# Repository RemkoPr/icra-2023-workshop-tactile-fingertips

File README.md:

# ICRA2023 Transferability in Robotics Workshop 
## Augmenting Off-the-Shelf Grippers with Tactile Sensing
[Paper](https://doi.org/10.48550/arXiv.2306.05902) -- [Related work](https://doi.org/10.1109/LRA.2023.3284382)

The development of tactile sensing ad its fusion with computer vision is expected to enhance robotic systems in handling complex tasks like deformable object manipulation. However, readily available industrial grippers typically lack tactile feedback, which has led researchers to integrate and develop their own tactile sensors. This has resulted in a wide range of sensor hardware and difficulty in comparing tasksolving performance. We propose moving towards accessible open-source sensors and present a set of fingertips specifically designed for fine object manipulation, with readily interpretable data output. The fingertips are validated through two difficult tasks: cloth edge tracing and cable tracing. 

## Video material
Video material of the proof-of-concept experiments is provided in the videos folder.

## Hardware integration

Currently the fingertips are designed for the Robotiq-2F85 gripper. This gripper can be mounted to various different collaborative robot arms by means of a tool flange. We provide a design for an intermediate flange, nestled between the Robotiq tool flange and the gripper itself, that provides external interfaces for the supply and ground pins otherwise reserved for the gripper. This way, the sensorised fingertips can draw their power straight from the robot arm. The intermediate flange consists of a pcb in the cad/pcb folder and two 3D printed parts in the cad/3d folder. Sensor readout is currently performed by an Arduino Nano 33 BLE externally mounted to the gripper via a 3D printed holder (see cad/3d), but we are in the process of integrating a microcontroller on our custom intermediate flange such that sensor readout and data transmission can also be done internally.  

<BR CLEAR="all">

## Software integration
Both Arduino firmware and python readout software is provided. Data is communicated between the arduino and a remote workstation via Bluetooth Low Energy. Further documentation on the software is provided in the code/python folder.

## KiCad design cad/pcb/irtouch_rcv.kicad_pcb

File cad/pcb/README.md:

This folder contains PCB design files for both the receiver (irtouch_led) as well as the tranmitter (irtouch_rcv) tactile finger. Additionally, the design for the custom breakout flange (robotiq_wrist_coupling) PCB is provided. This PCB is set between the Robotiq I/O Coupling and the 2F-85 gripper itself. The arduino_breakout is a simple PCB to which female 0.1" pin headers are soldered. This PCB fits in the Arduino_holder found in cad/3d.

Refer to the cad/3d folder for an exploded view of the structural integration.

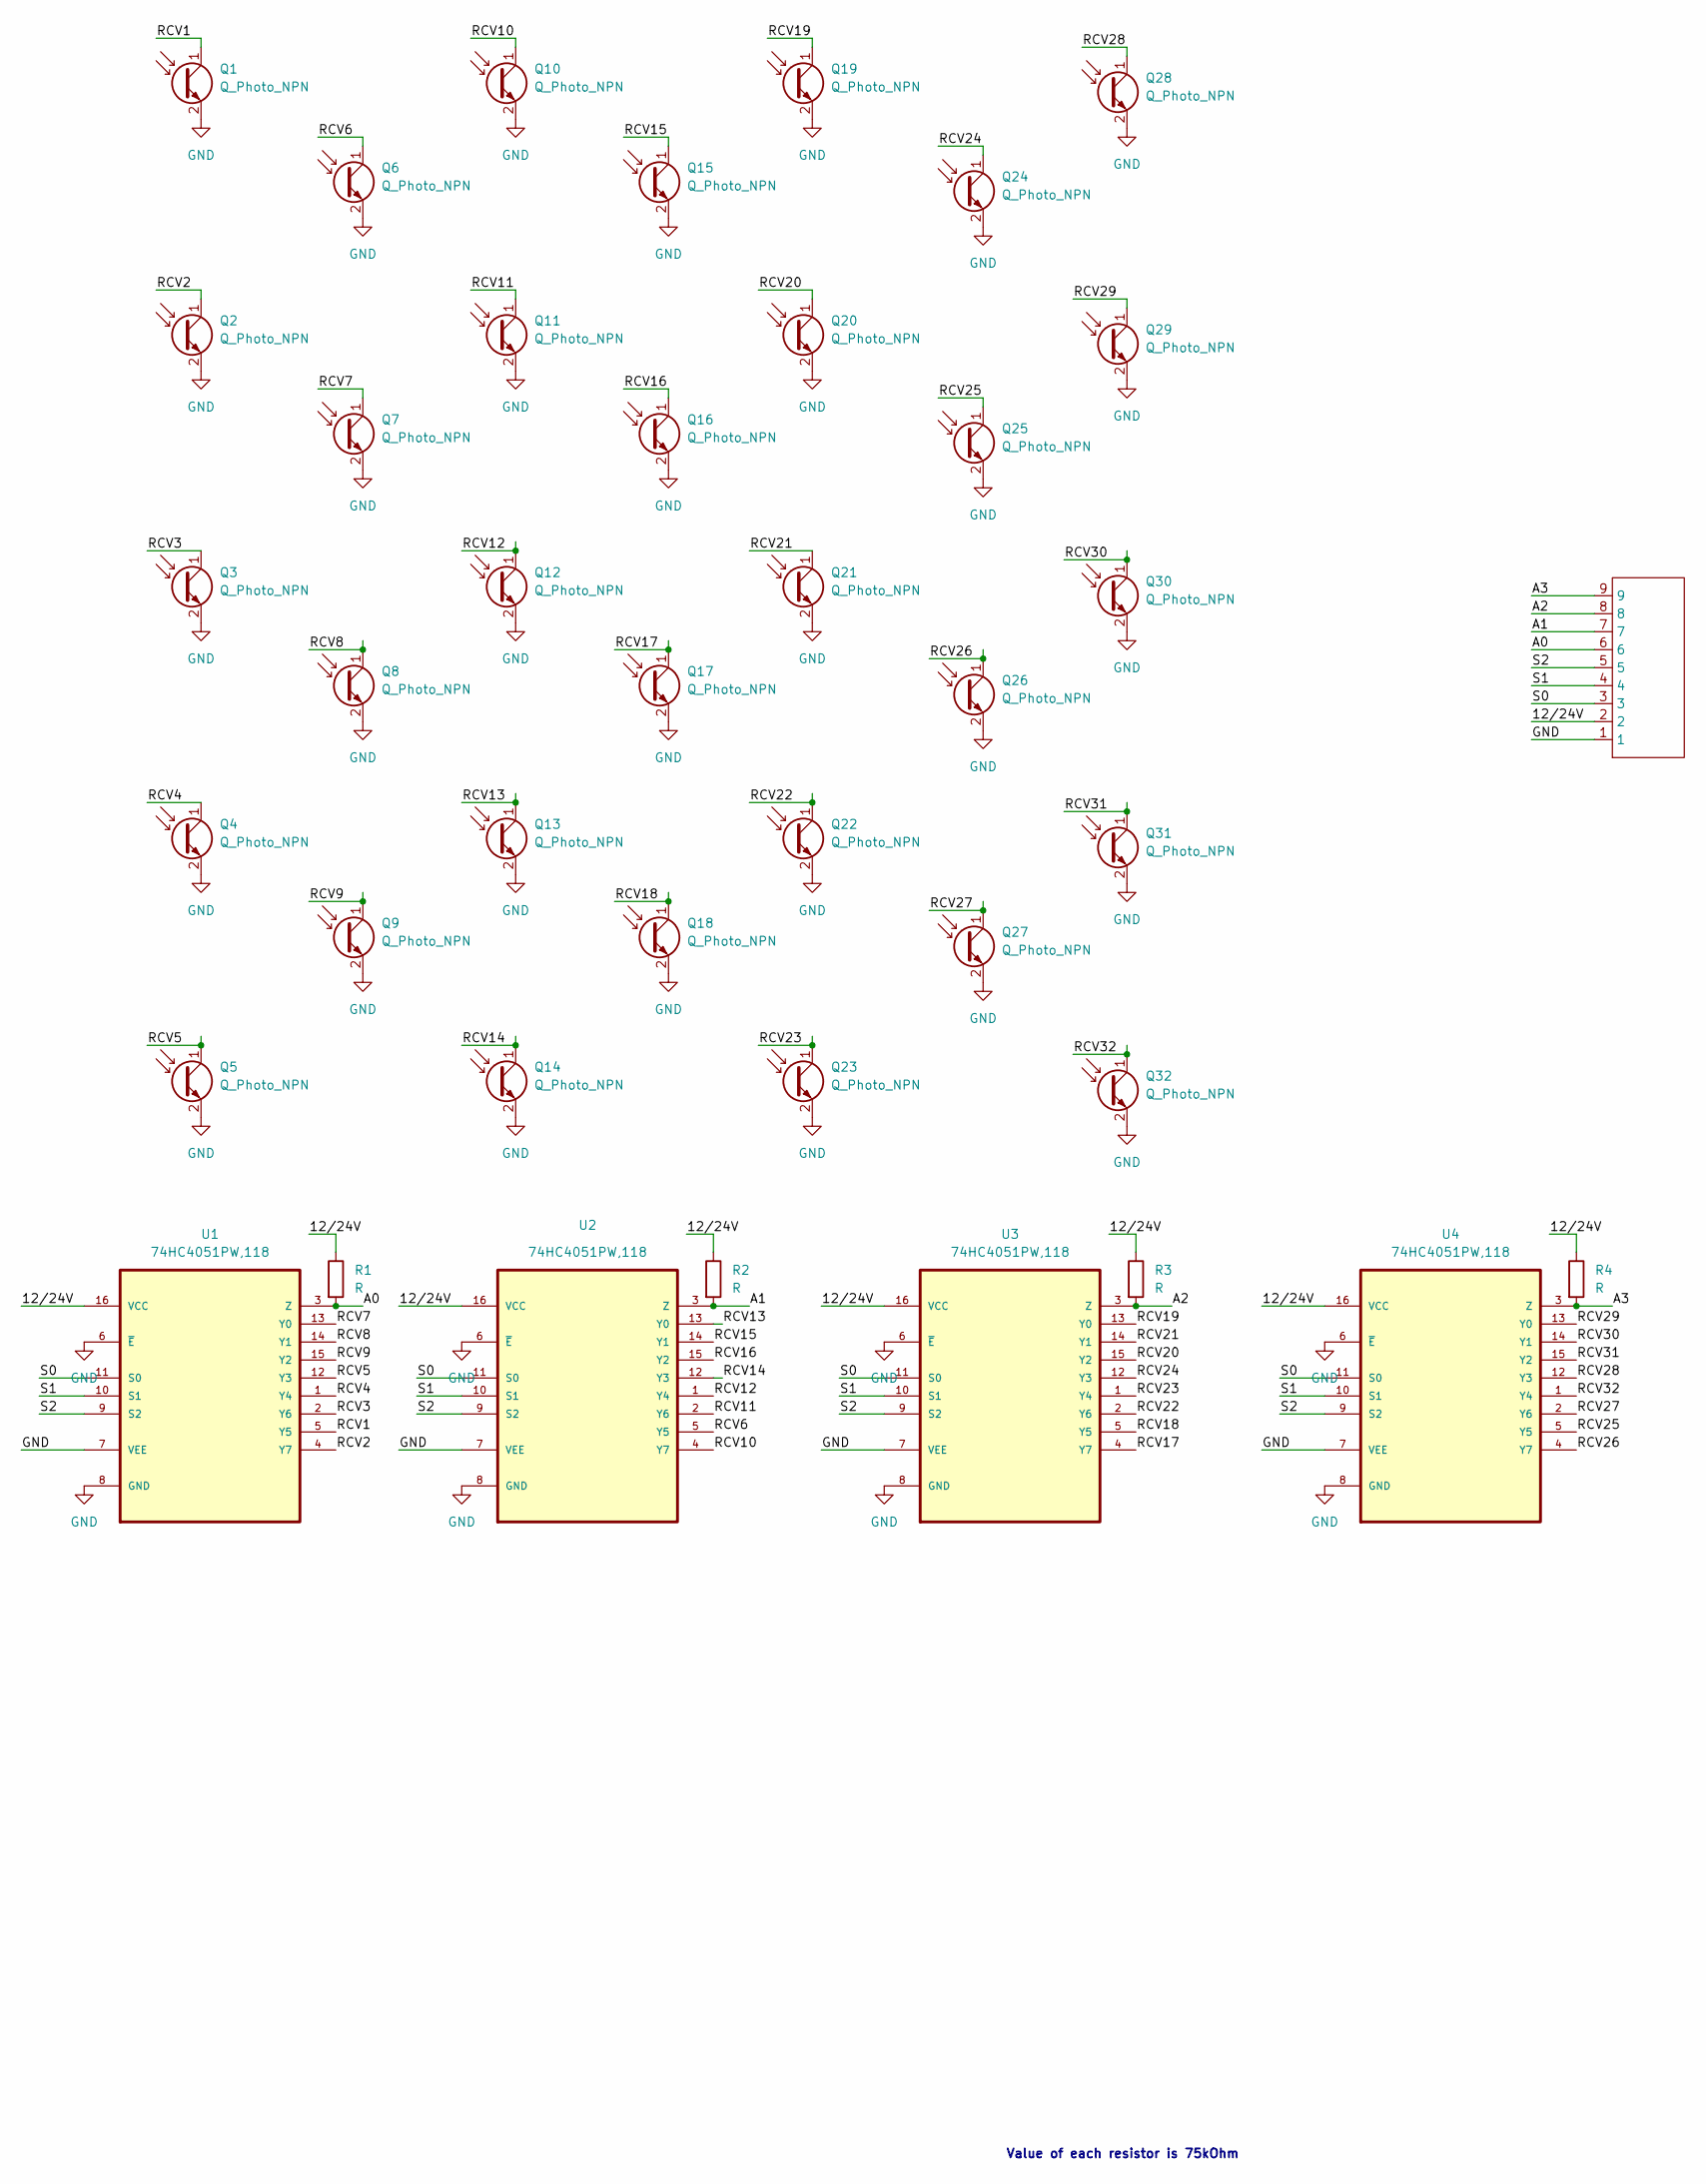
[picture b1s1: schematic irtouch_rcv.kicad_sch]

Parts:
I1: 9POS_INTERFACE
Q1, Q2, Q3, Q4, Q5, Q6, Q7, Q8, Q9, Q10, Q11, Q12, Q13, Q14, Q15, Q16, Q17, Q18, Q19, Q20, Q21, Q22, Q23, Q24, Q25, Q26, Q27, Q28, Q29, Q30, Q31, Q32: Q_Photo_NPN; RCVR
R1, R2, R3, R4: R; R0603
U1, U2, U3, U4: 74HC4051PW,118; SOP65P640X110-16N; MPN 74HC4051PW,118

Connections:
/12/24V: I1.2, R1.1, R2.1, R3.1, R4.1, U1.16 (VCC), U2.16 (VCC), U3.16 (VCC), U4.16 (VCC)
/A0: I1.6, R1.2, U1.3 (Z)
/A1: I1.7, R2.2, U2.3 (Z)
/A2: I1.8, R3.2, U3.3 (Z)
/A3: I1.9, R4.2, U4.3 (Z)
/RCV1: Q1.1 (C), U1.5 (Y5)
/RCV2: Q2.1 (C), U1.4 (Y7)
/RCV3: Q3.1 (C), U1.2 (Y6)
/RCV4: Q4.1 (C), U1.1 (Y4)
/RCV5: Q5.1 (C), U1.12 (Y3)
/RCV6: Q6.1 (C), U2.5 (Y5)
/RCV7: Q7.1 (C), U1.13 (Y0)
/RCV8: Q8.1 (C), U1.14 (Y1)
/RCV9: Q9.1 (C), U1.15 (Y2)
/RCV10: Q10.1 (C), U2.4 (Y7)
/RCV11: Q11.1 (C), U2.2 (Y6)
/RCV12: Q12.1 (C), U2.1 (Y4)
/RCV13: Q13.1 (C), U2.13 (Y0)
/RCV14: Q14.1 (C), U2.12 (Y3)
/RCV15: Q15.1 (C), U2.14 (Y1)
/RCV16: Q16.1 (C), U2.15 (Y2)
/RCV17: Q17.1 (C), U3.4 (Y7)
/RCV18: Q18.1 (C), U3.5 (Y5)
/RCV19: Q19.1 (C), U3.13 (Y0)
/RCV20: Q20.1 (C), U3.15 (Y2)
/RCV21: Q21.1 (C), U3.14 (Y1)
/RCV22: Q22.1 (C), U3.2 (Y6)
/RCV23: Q23.1 (C), U3.1 (Y4)
/RCV24: Q24.1 (C), U3.12 (Y3)
/RCV25: Q25.1 (C), U4.5 (Y5)
/RCV26: Q26.1 (C), U4.4 (Y7)
/RCV27: Q27.1 (C), U4.2 (Y6)
/RCV28: Q28.1 (C), U4.12 (Y3)
/RCV29: Q29.1 (C), U4.13 (Y0)
/RCV30: Q30.1 (C), U4.14 (Y1)
/RCV31: Q31.1 (C), U4.15 (Y2)
/RCV32: Q32.1 (C), U4.1 (Y4)
/S0: I1.3, U1.11 (S0), U2.11 (S0), U3.11 (S0), U4.11 (S0)
/S1: I1.4, U1.10 (S1), U2.10 (S1), U3.10 (S1), U4.10 (S1)
/S2: I1.5, U1.9 (S2), U2.9 (S2), U3.9 (S2), U4.9 (S2)
GND: I1.1, Q1.2 (E), Q2.2 (E), Q3.2 (E), Q4.2 (E), Q5.2 (E), Q6.2 (E), Q7.2 (E), Q8.2 (E), Q9.2 (E), Q10.2 (E), Q11.2 (E), Q12.2 (E), Q13.2 (E), Q14.2 (E), Q15.2 (E), Q16.2 (E), Q17.2 (E), Q18.2 (E), Q19.2 (E), Q20.2 (E), Q21.2 (E), Q22.2 (E), Q23.2 (E), Q24.2 (E), Q25.2 (E), Q26.2 (E), Q27.2 (E), Q28.2 (E), Q29.2 (E), Q30.2 (E), Q31.2 (E), Q32.2 (E), U1.6 (~E), U1.7 (VEE), U1.8 (GND), U2.6 (~E), U2.7 (VEE), U2.8 (GND), U3.6 (~E), U3.7 (VEE), U3.8 (GND), U4.6 (~E), U4.7 (VEE), U4.8 (GND)

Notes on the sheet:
Value of each resistor is 75kOhm

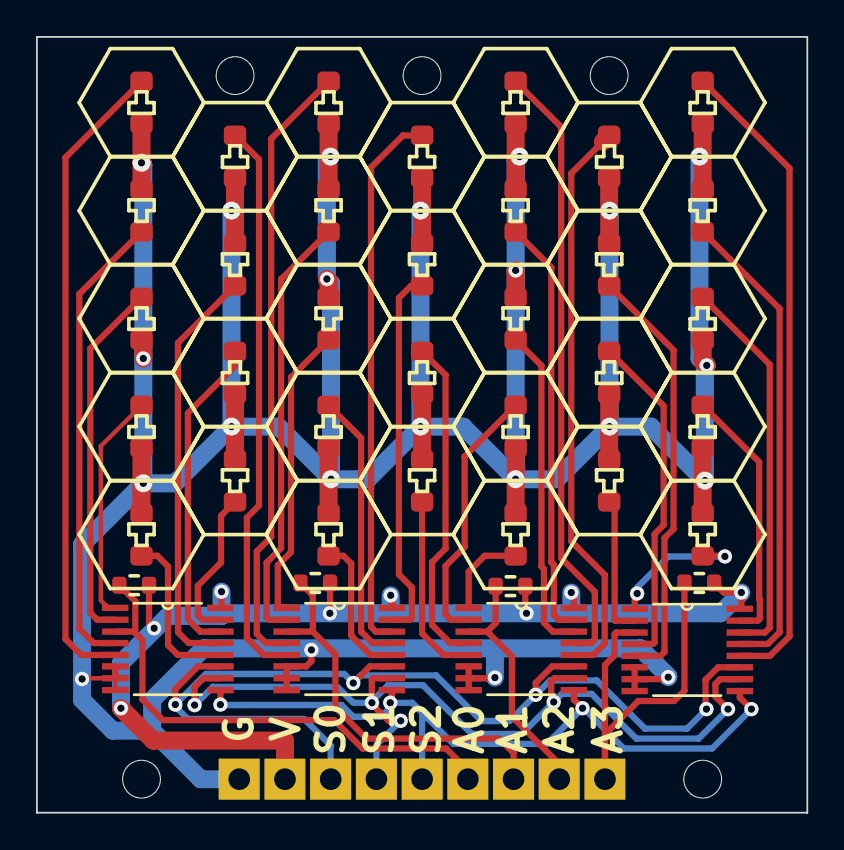
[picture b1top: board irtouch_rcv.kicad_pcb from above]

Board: 4 copper layers, 42.8 x 43.1 mm, 41 parts (0 on the bottom side), 41 nets.

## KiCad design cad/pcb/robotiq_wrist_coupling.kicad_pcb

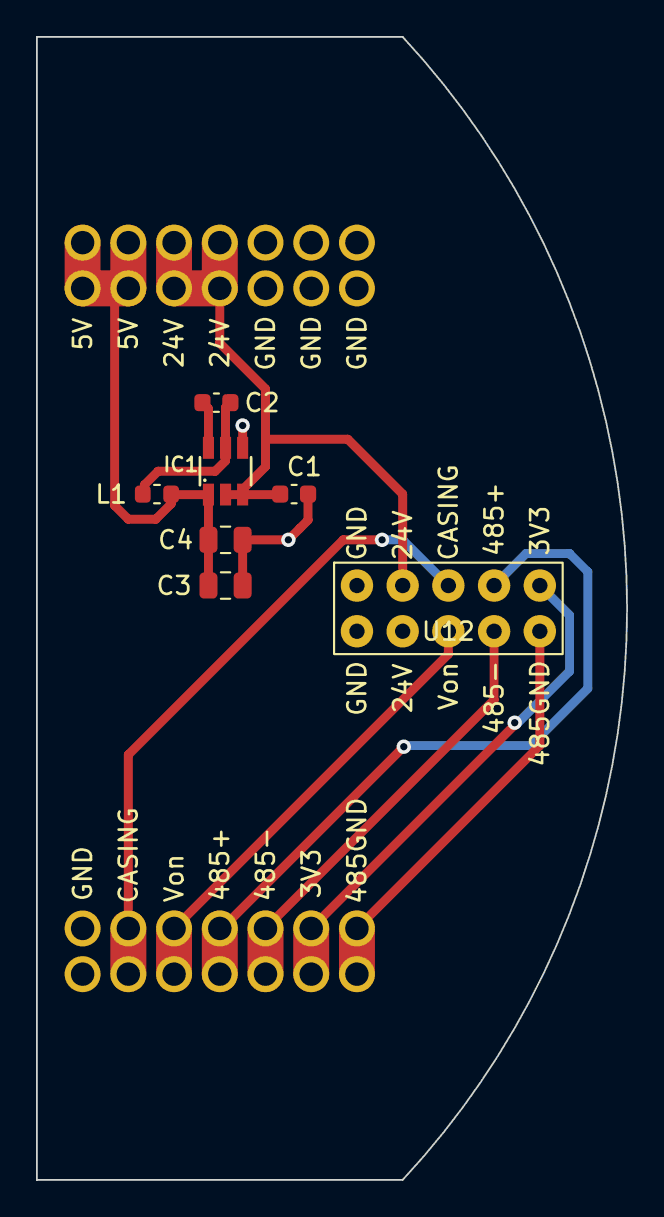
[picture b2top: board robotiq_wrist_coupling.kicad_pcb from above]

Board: 2 copper layers, 32.8 x 63.5 mm, 35 parts (0 on the bottom side), 11 nets.

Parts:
C1: 10µF; C_0603_1608Metric
C2: 100nF; C_0603_1608Metric
C3, C4: 22µF; C_0805_2012Metric
IC1: AP63205; TSOT23-6
L1: 4µ7; L_0603_1608Metric
U1, U2, U2#2, U3, U3#2, U4, U5, U5#2, U6, U7, U8, U9, U10, U11, U13, U14, U15, U15#2, U16, U16#2, U17, U18, U19, U20, U21, U21#2, U22, U22#2: HOLE
U12: 10PIN_SPRING_HEADER

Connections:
/3V3_out: U10.1, U11.1, U12.9
/5V: C3.1, C4.1, IC1.1 (FB), L1.2, U21.1, U21#2.1, U22.1, U22#2.1
/24V: C1.1, IC1.2 (EN), IC1.3 (VIN), U12.3, U15.1, U15#2.1, U16.1, U16#2.1
/485+: U8.1, U9.1, U12.7
/485-: U12.8, U14.1, U18.1
/485GND: U12.10, U19.1, U20.1
/CASING: U6.1, U7.1, U12.5
/Von: U12.6, U13.1, U17.1
GND: C1.2, C3.2, C4.2, IC1.4 (GND), U1.1, U2.1, U2#2.1, U3.1, U3#2.1, U4.1, U5.1, U5#2.1, U12.1, U12.2
unnamed: C2.1, IC1.6 (BST)
unnamed: C2.2, IC1.5 (SW), L1.1

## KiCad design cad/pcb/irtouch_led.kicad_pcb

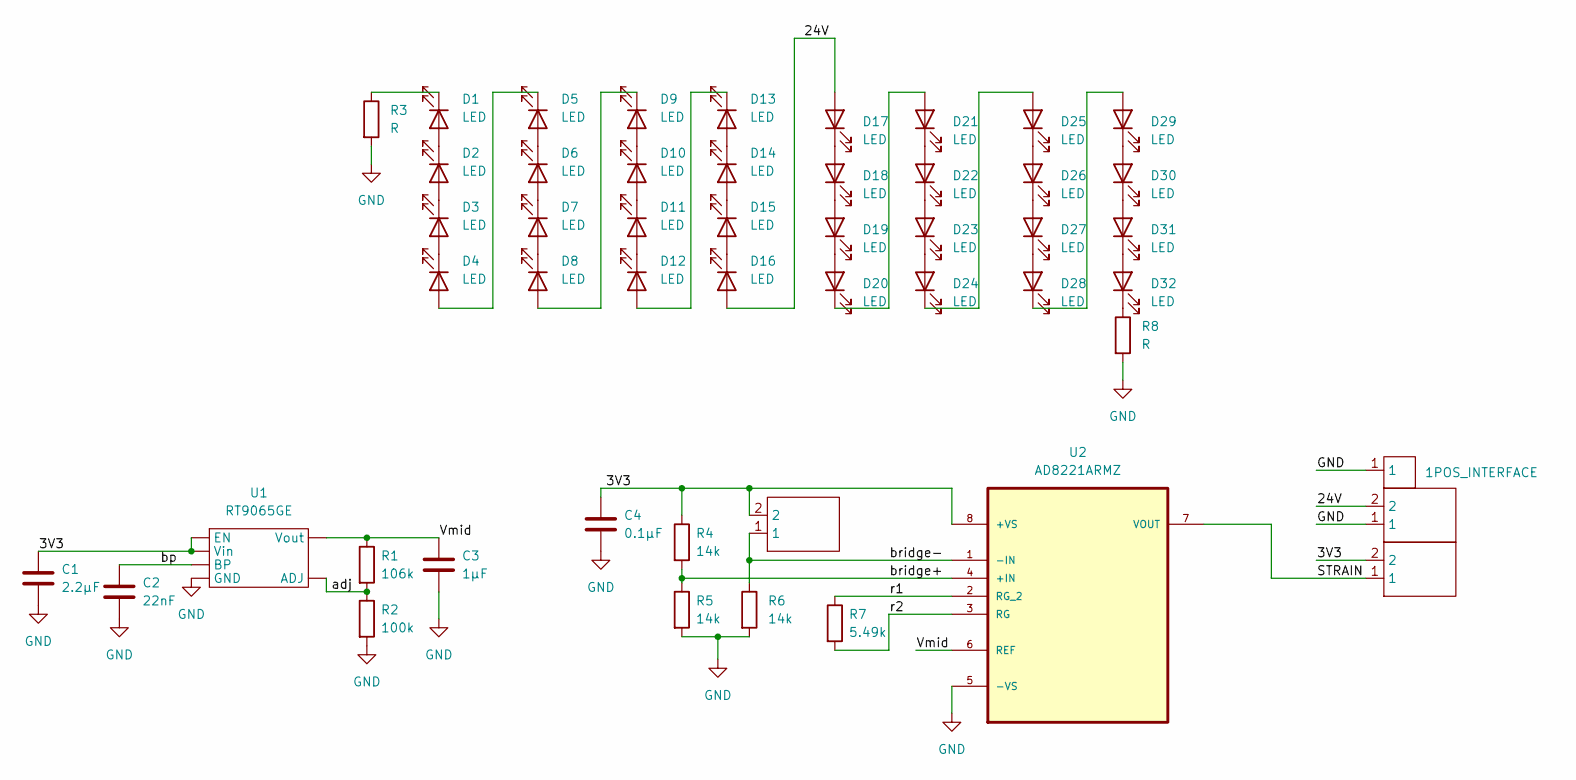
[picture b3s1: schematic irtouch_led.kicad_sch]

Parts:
C1: 2.2µF; C_0603_1608Metric
C2: 22nF; C_0603_1608Metric
C3: 1µF; C_0603_1608Metric
C4: 0.1µF; C_0603_1608Metric
D1, D2, D3, D4, D5, D6, D7, D8, D9, D10, D11, D12, D13, D14, D15, D16, D17, D18, D19, D20, D21, D22, D23, D24, D25, D26, D27, D28, D29, D30, D31, D32: LED; LED0603
I1: 2POS_INTERFACE; 2POS_STRAIN_INTERFACE
I2, I3: 2POS_INTERFACE
R1: 106k; R_0603_1608Metric
R2: 100k; R_0603_1608Metric
R3, R8: R; R_0603_1608Metric
R4, R5, R6: 14k; R_0603_1608Metric
R7: 5.49k; R_0603_1608Metric
U1: RT9065GE; SOT-23-6
U2: AD8221ARMZ; SOP65P490X110-8N; MPN AD8221ARMZ
U3: 1POS_INTERFACE

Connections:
/3V3: C1.1, C4.1, I1.2, I3.2, R4.1, U1.1 (Vin), U1.3 (EN), U2.8 (+VS)
/24V: D16.2 (A), D17.2 (A), I2.2
/STRAIN: I3.1, U2.7 (VOUT)
/Vmid: C3.1, R1.1, U1.6 (Vout), U2.6 (REF)
/adj: R1.2, R2.1, U1.5 (ADJ)
/bp: C2.1, U1.4 (BP)
/bridge+: R4.2, R5.1, U2.4 (+IN)
/bridge-: I1.1, R6.1, U2.1 (-IN)
/r1: R7.1, U2.2 (RG_2)
/r2: R7.2, U2.3 (RG)
GND: C1.2, C2.2, C3.2, C4.2, I2.1, R2.2, R3.2, R5.2, R6.2, R8.2, U1.2 (GND), U2.5 (-VS), U3.1
unnamed: D1.1 (K), R3.1
unnamed: D1.2 (A), D2.1 (K)
unnamed: D2.2 (A), D3.1 (K)
unnamed: D3.2 (A), D4.1 (K)
unnamed: D4.2 (A), D5.1 (K)
unnamed: D5.2 (A), D6.1 (K)
unnamed: D6.2 (A), D7.1 (K)
unnamed: D7.2 (A), D8.1 (K)
unnamed: D8.2 (A), D9.1 (K)
unnamed: D9.2 (A), D10.1 (K)
unnamed: D10.2 (A), D11.1 (K)
unnamed: D11.2 (A), D12.1 (K)
unnamed: D12.2 (A), D13.1 (K)
unnamed: D13.2 (A), D14.1 (K)
unnamed: D14.2 (A), D15.1 (K)
unnamed: D15.2 (A), D16.1 (K)
unnamed: D17.1 (K), D18.2 (A)
unnamed: D18.1 (K), D19.2 (A)
unnamed: D19.1 (K), D20.2 (A)
unnamed: D20.1 (K), D21.2 (A)
unnamed: D21.1 (K), D22.2 (A)
unnamed: D22.1 (K), D23.2 (A)
unnamed: D23.1 (K), D24.2 (A)
unnamed: D24.1 (K), D25.2 (A)
unnamed: D25.1 (K), D26.2 (A)
unnamed: D26.1 (K), D27.2 (A)
unnamed: D27.1 (K), D28.2 (A)
unnamed: D28.1 (K), D29.2 (A)
unnamed: D29.1 (K), D30.2 (A)
unnamed: D30.1 (K), D31.2 (A)
unnamed: D31.1 (K), D32.2 (A)
unnamed: D32.1 (K), R8.1

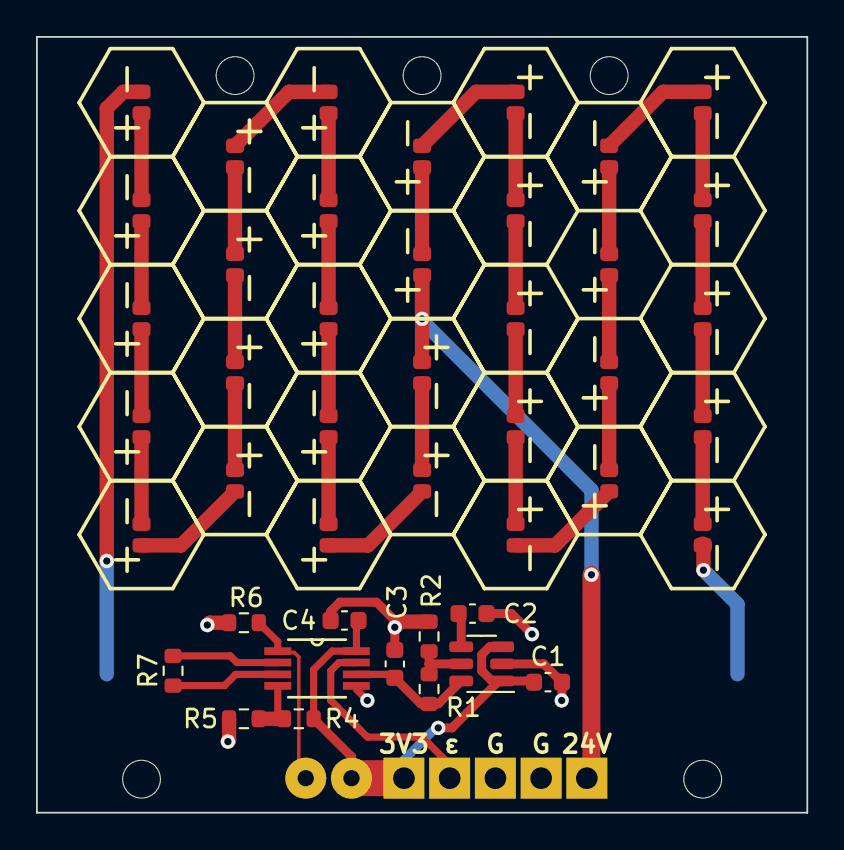
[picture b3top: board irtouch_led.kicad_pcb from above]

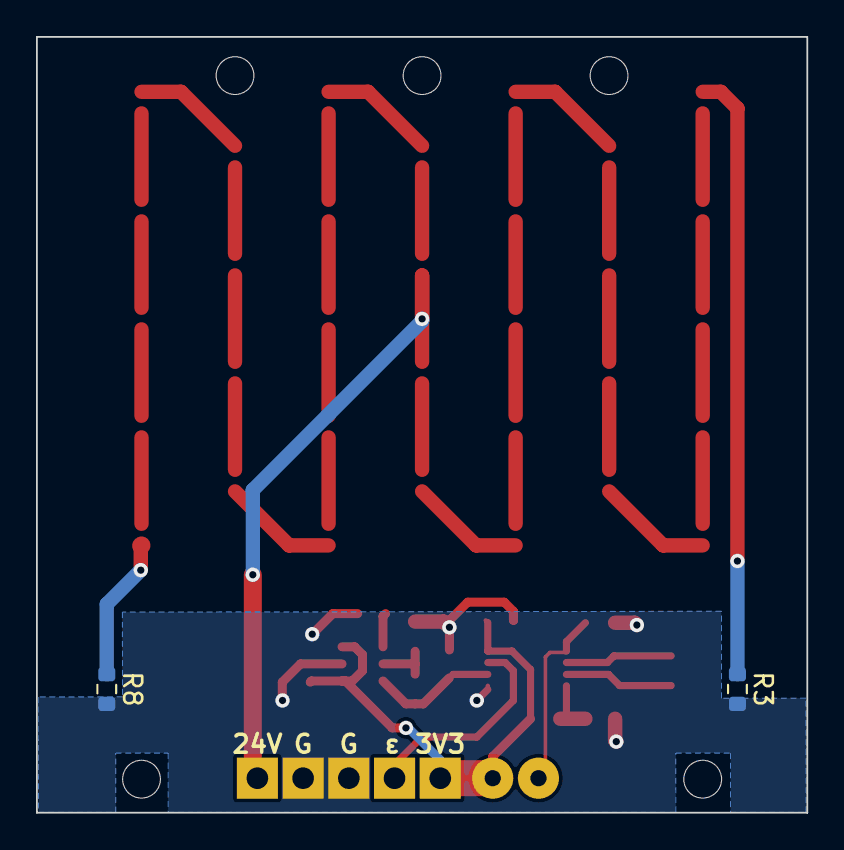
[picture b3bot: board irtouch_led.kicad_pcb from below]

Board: 2 copper layers, 42.8 x 43.1 mm, 50 parts (2 on the bottom side), 43 nets.

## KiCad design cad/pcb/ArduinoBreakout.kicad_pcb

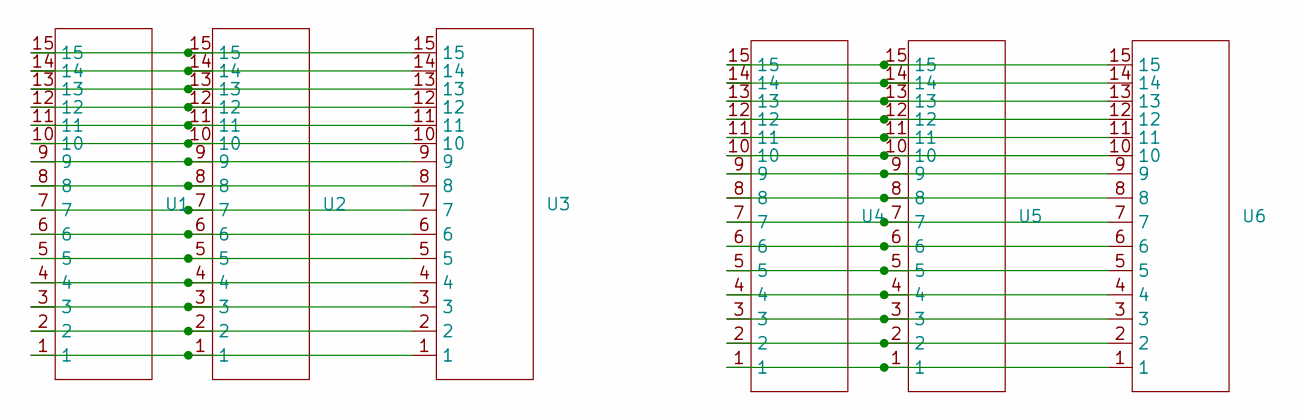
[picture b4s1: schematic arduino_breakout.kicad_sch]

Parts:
U1, U2, U3, U4, U5, U6: 15POS_INTERFACE

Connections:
unnamed: U1.1, U2.1, U3.1
unnamed: U1.2, U2.2, U3.2
unnamed: U1.3, U2.3, U3.3
unnamed: U1.4, U2.4, U3.4
unnamed: U1.5, U2.5, U3.5
unnamed: U1.6, U2.6, U3.6
unnamed: U1.7, U2.7, U3.7
unnamed: U1.8, U2.8, U3.8
unnamed: U1.9, U2.9, U3.9
unnamed: U1.10, U2.10, U3.10
unnamed: U1.11, U2.11, U3.11
unnamed: U1.12, U2.12, U3.12
unnamed: U1.13, U2.13, U3.13
unnamed: U1.14, U2.14, U3.14
unnamed: U1.15, U2.15, U3.15
unnamed: U4.1, U5.1, U6.1
unnamed: U4.2, U5.2, U6.2
unnamed: U4.3, U5.3, U6.3
unnamed: U4.4, U5.4, U6.4
unnamed: U4.5, U5.5, U6.5
unnamed: U4.6, U5.6, U6.6
unnamed: U4.7, U5.7, U6.7
unnamed: U4.8, U5.8, U6.8
unnamed: U4.9, U5.9, U6.9
unnamed: U4.10, U5.10, U6.10
unnamed: U4.11, U5.11, U6.11
unnamed: U4.12, U5.12, U6.12
unnamed: U4.13, U5.13, U6.13
unnamed: U4.14, U5.14, U6.14
unnamed: U4.15, U5.15, U6.15

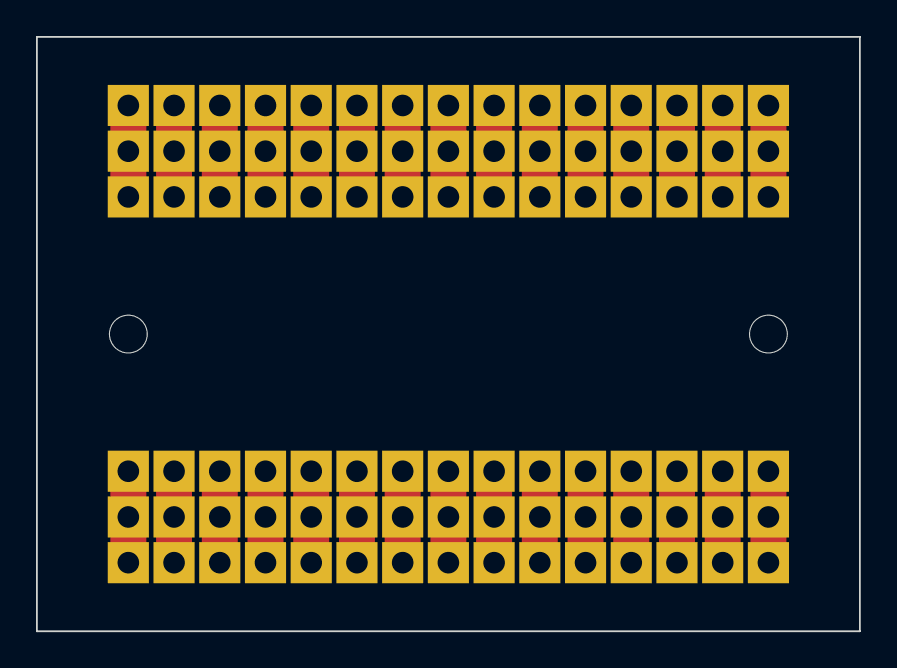
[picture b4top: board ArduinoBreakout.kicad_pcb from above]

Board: 2 copper layers, 45.7 x 33.0 mm, 6 parts (0 on the bottom side), 30 nets.

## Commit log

2023-04-07 added videos
2023-04-07 added arduino code, python code and pcb files
2023-04-09 added 3d files
2023-04-09 updated 3d files
2023-04-11 updated 3D designs
2023-04-11 updated cad/3d/README.md
2023-04-12 added Arduino breakout pcb, updated irtouch_rcv design to 2-layer
2023-04-12 Rename ArduinoBreakout.kicad_pcb to arduino_breakout.kicad_pcb
2023-04-12 Rename ArduinoBreakout.kicad_sch to arduino_breakout.kicad_sch
2023-05-11 added assembly manual
2023-05-16 updated assembly manual
2023-05-18 finished assembly manuals
2023-05-18 started poster
2023-05-18 updated poster
2023-05-19 updated collapsed and exploded view imgs
2023-05-19 updqted poster
2023-05-24 finished poster
2023-05-24 updated exploded view
2023-05-29 Added PCB BOM
2023-05-31 added paper pdf
2024-10-01 cropped img
